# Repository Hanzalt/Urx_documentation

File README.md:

# Urx_documentation
Welcome to the Urx_documentation! You may be wondering what URX is. URX is first completely open source console. This means that if you want to, you can create it by yourself and completly for FREE. The case is printed on a 3D printer. Electrical components are imported from China and from GM electronics.

To find out more, go to the wiki!

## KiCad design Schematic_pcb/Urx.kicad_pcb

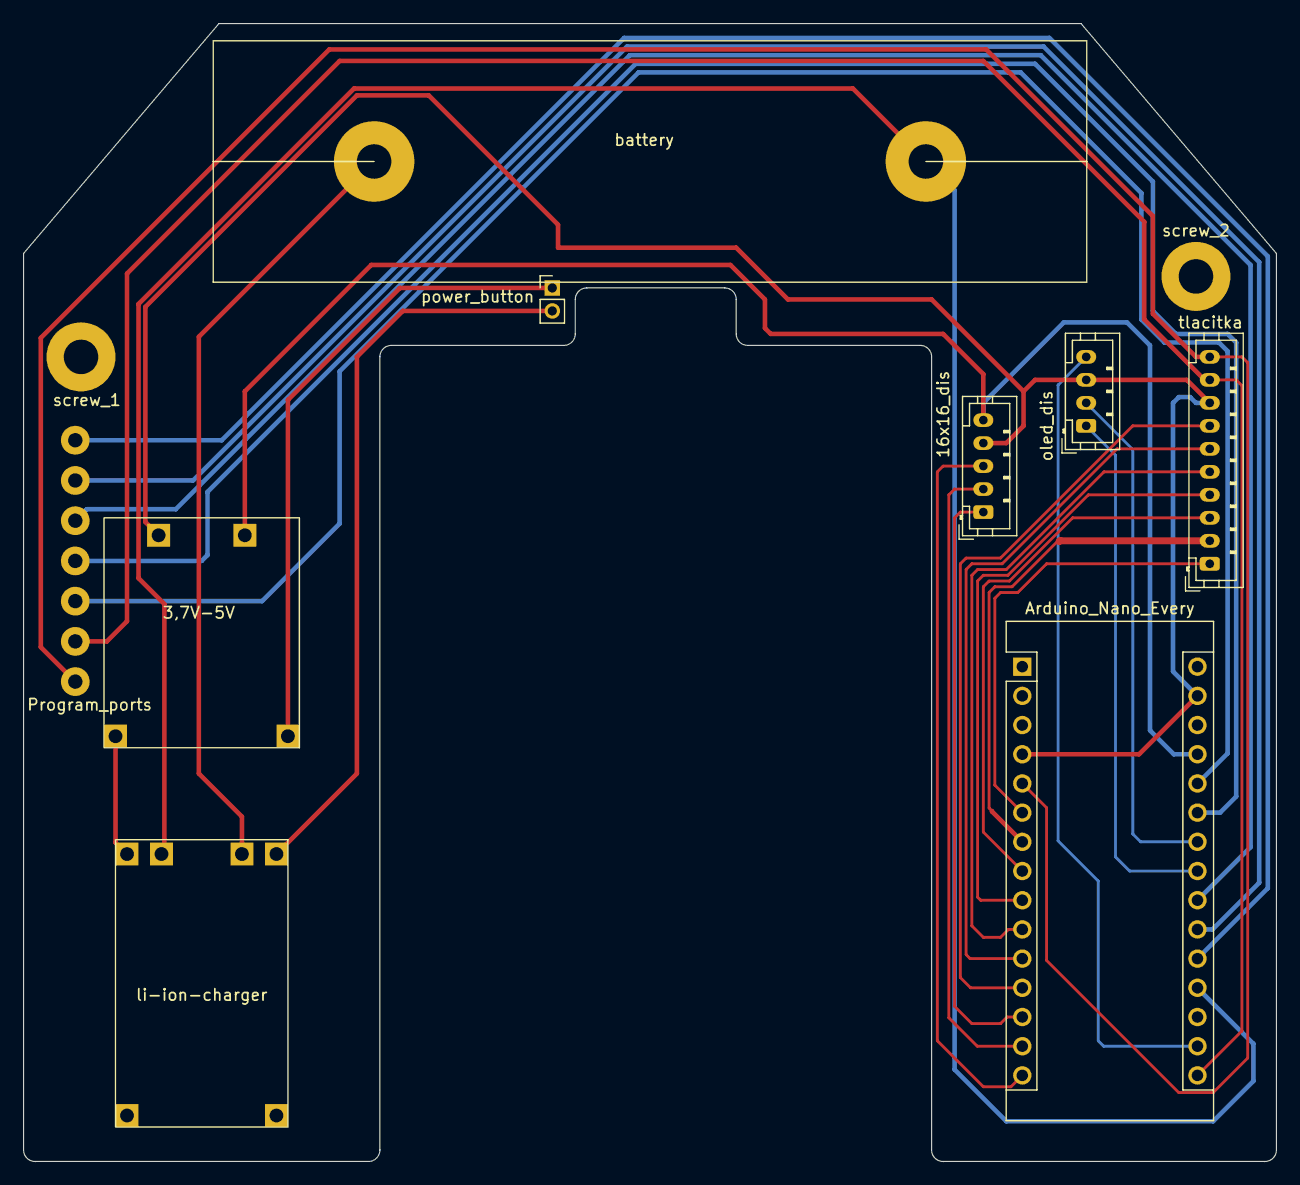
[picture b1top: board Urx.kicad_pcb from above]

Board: 2 copper layers, 109.0 x 99.0 mm, 11 parts (0 on the bottom side), 27 nets.

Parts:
3,7V-5V: boost-to-5v
16x16_dis: 5_pin; JST_PH_B5B-PH-K_1x05_P2.00mm_Vertical
Arduino_Nano_Every: Arduino_Nano_Every; Arduino_Nano
Program_ports: 7_pin
battery: battery_li-ion; li-ion_battery
li-ion-charger: li-ion-charger
oled_dis: 4_pin; JST_PH_B4B-PH-K_1x04_P2.00mm_Vertical
power_button: 2_pin; PinHeader_1x02_P2.00mm_Vertical
screw_1, screw_2: MountingHole_3mm_Pad
tlacitka: 10_pin; JST_PH_B10B-PH-K_1x10_P2.00mm_Vertical

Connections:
2: Arduino_Nano_Every.5 (D2), Program_ports.7 (2), tlacitka.10 (n2)
13: Arduino_Nano_Every.16 (SCK), Program_ports.6 (13), tlacitka.9 (n1)
+3V3: Arduino_Nano_Every.17 (3V3), oled_dis.4 (3,3V)
+5V: 3,7V-5V.1 (5V), 16x16_dis.5 (5V), Arduino_Nano_Every.27 (+5V)
ABat: Arduino_Nano_Every.19 (A0), battery.2 (5V), li-ion-charger.1 (B+)
GND: 3,7V-5V.2 (GND), 16x16_dis.4 (gnd), Arduino_Nano_Every.4 (GND), Arduino_Nano_Every.29 (GND), oled_dis.3 (gnd), tlacitka.8 (gnd)
unnamed: 3,7V-5V.3 (IN+), li-ion-charger.5 (OUT+)
unnamed: 3,7V-5V.4 (IN-), power_button.1 (gnd1)
unnamed: 16x16_dis.1 (cs), Arduino_Nano_Every.13 (D10)
unnamed: 16x16_dis.2 (din), Arduino_Nano_Every.14 (MOSI)
unnamed: 16x16_dis.3 (clk), Arduino_Nano_Every.15 (MISO)
unnamed: Arduino_Nano_Every.6 (D3), tlacitka.1 (b)
unnamed: Arduino_Nano_Every.7 (D4), tlacitka.2 (sound)
unnamed: Arduino_Nano_Every.8 (D5), tlacitka.3 (down)
unnamed: Arduino_Nano_Every.9 (D6), tlacitka.4 (left)
unnamed: Arduino_Nano_Every.10 (D7), tlacitka.5 (forward)
unnamed: Arduino_Nano_Every.11 (D8), tlacitka.6 (right)
unnamed: Arduino_Nano_Every.12 (D9), tlacitka.7 (a)
unnamed: Arduino_Nano_Every.20 (A1), Program_ports.1 (A1)
unnamed: Arduino_Nano_Every.21 (A2), Program_ports.2 (A2)
unnamed: Arduino_Nano_Every.22 (A3), Program_ports.3 (A3)
unnamed: Arduino_Nano_Every.23 (SDA/A4), oled_dis.1 (sda)
unnamed: Arduino_Nano_Every.24 (SCL/A5), oled_dis.2 (csk)
unnamed: Arduino_Nano_Every.25 (A6), Program_ports.4 (A6)
unnamed: Arduino_Nano_Every.26 (A7), Program_ports.5 (A7)
unnamed: battery.1 (gnd), li-ion-charger.2 (B-)
unnamed: li-ion-charger.6 (OUT-), power_button.2 (gnd2)

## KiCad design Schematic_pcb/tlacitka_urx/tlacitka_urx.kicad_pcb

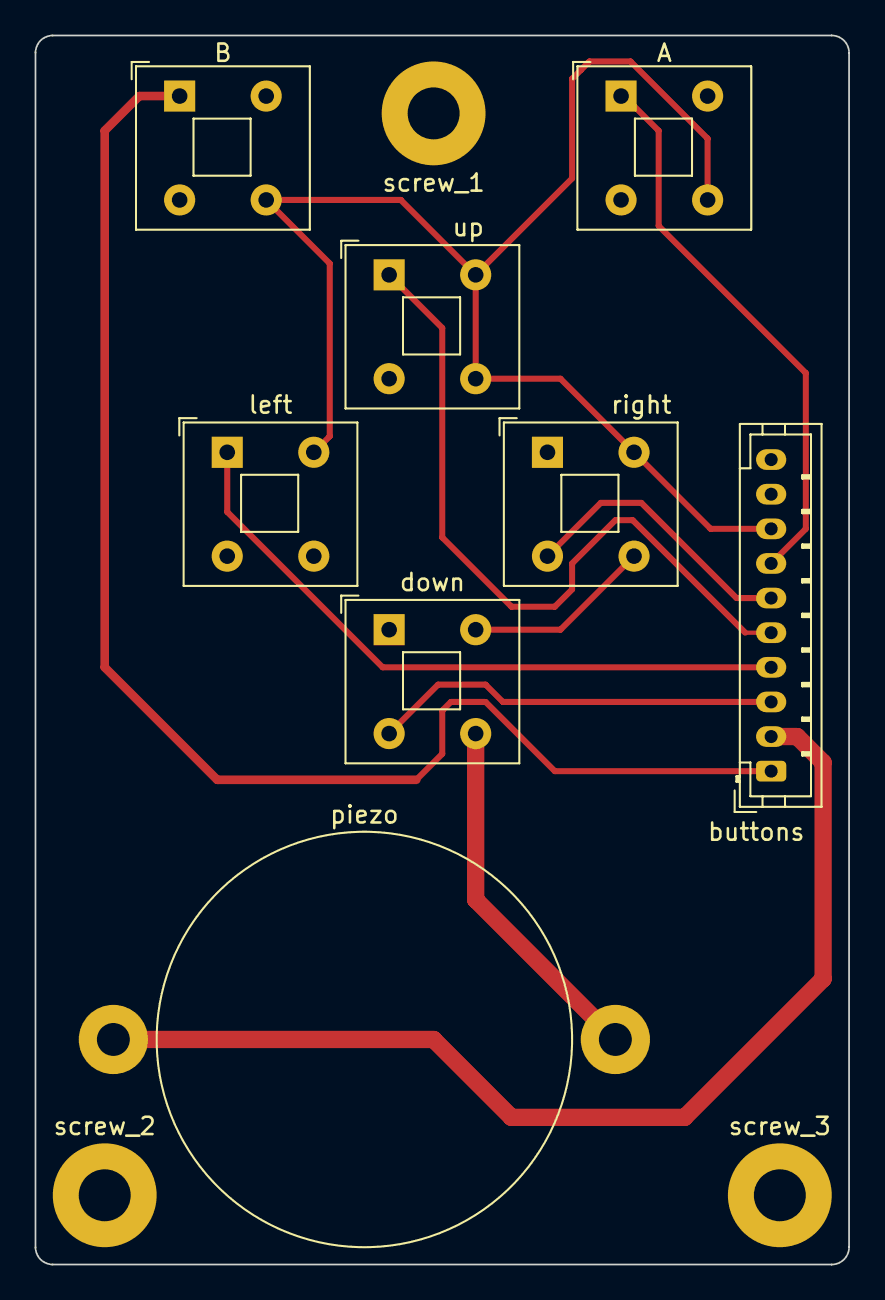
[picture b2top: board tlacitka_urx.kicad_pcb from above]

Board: 2 copper layers, 47.0 x 71.0 mm, 11 parts (0 on the bottom side), 10 nets.

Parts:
A: SW_Push_Dual; SW_Push_2P1T_Toggle_CK_PVA1xxH1xxxxxxV2
B: SW_Push_Dual; SW_Push_2P1T_Toggle_CK_PVA1xxH1xxxxxxV2
buttons: 10_pin; JST_PH_B10B-PH-K_1x10_P2.00mm_Vertical
down: SW_Push_Dual; SW_Push_2P1T_Toggle_CK_PVA1xxH1xxxxxxV2
left: SW_Push_Dual; SW_Push_2P1T_Toggle_CK_PVA1xxH1xxxxxxV2
piezo: Piezo_KPEG110
right: SW_Push_Dual; SW_Push_2P1T_Toggle_CK_PVA1xxH1xxxxxxV2
screw_1, screw_2, screw_3: MountingHole_3mm_Pad
up: SW_Push_Dual; SW_Push_2P1T_Toggle_CK_PVA1xxH1xxxxxxV2

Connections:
unnamed: A.1, buttons.7 (a)
unnamed: A.4, B.4, buttons.8 (gnd), left.2, right.2, up.2, up.4
unnamed: B.1, buttons.1 (b)
unnamed: down.2, right.4
unnamed: buttons.3 (down), down.3
unnamed: buttons.4 (left), left.1
unnamed: down.4, piezo.1 (Gnd)
unnamed: buttons.6 (right), right.3
unnamed: buttons.2 (sound), piezo.2
unnamed: buttons.5 (forward), up.1

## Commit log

2022-02-22 Create PCB_naming
2022-02-22 Update PCB_naming
    adding din
2022-05-04 0-4
    urxos_0-4
    +Galaxian
    +nove menu
    -Dekuje e
2022-08-10 Vytvoreni knihovny
    +Snaha o vytvoreni jedne knihovny - co nejjednoduseji udelany kod - vse schovany v jedne knihovne (inicializace, funkce)
    +Vytvoreni testovaciho kodu
    +Zip soubor knihoven
2022-08-12 nefunkcni pokus s knihovnou
2022-08-21 test
2022-08-21 Funkcni verze s knihovnou v1
2022-08-25 Snaha o udelani interruptu
    Nakonec jsem zjistil ze to je hardwerova chyba
2022-08-25 Smazal jsem space invators
2022-08-26 BIG UPDATE
    Zmeneny nazev z code na urxos. Zmeneny vykreslovaci algoritmus.
    Zmeneny ikonky,
    Zmeneny opening animation - logo a znelka
2022-08-27 Verze 0.6.0
    Zmeneny vsechny vykreslovaci funkce.
    Opraveno vsechno vykreslovani.
    Predelani zvuku.
    Dalsi opravy chyb
2022-08-28 Nastaveni a male zmeny
2022-08-28 Urx_0_6_1_library
2022-08-30 Settings
2022-08-30 DanceMan basic functionality
2022-08-31 DanceMan
    Vytvoreni dance mana
2022-08-31 UrxLibrary 0.7.9
2022-09-02 MIni update
2022-09-10 Making folders
2022-09-18 Flip display and library update
    I needed to flip display because I change the position of display (OLED 0.91"). Finally I managed to make one library.
2022-09-18 Rename folder code to Firmware
    I renamed folder code to Firmware because it was similar as github button code
2022-09-18 URXos_library_0-7-92
2022-10-08 Sound
    Turning sound off in Dance man when it should be turned off.
2022-10-11 Models
2022-10-11 Models_update
2022-10-21 score display mistake
2022-10-26 Library_0.7.9.3
    BIG library change - size of library decreased from 10.5 MB to 71.8 KB.
2022-10-27 Mistake-slower/bigger
2022-10-27 Revert "Mistake-slower/bigger"
    This reverts commit 092e83d06186fa26a2ec9a688647ae0a62e0e741.
2022-10-28 1. Removed file PCB_naming it was not important. 2. Remaped battery indicator. 3. new Difficulty tab in settings.
2022-10-28 1. Difficulty 2. Finally I managed to repair Danceman. YES
2022-10-29 1. app names 2. new gamemode selection in snake 3. new gamemode in snake - snake SUPER - snake with another food type
2022-10-29 1. New library 2. New readme in libraries
2022-10-29 1. Changed Medium intensity 2. Repaired bug in galaxian - sound
2022-11-01 1. bug fixes 2. DanceMan modes
2022-11-03 1. New songs 2. Big Galaxian update 3. New danceman songs
2022-11-04 1. Galaxian modes 2. New songs - Doom, Bloody tears 3. Bug fixes - high score menu
2022-11-07 1. New highscore celebration 2. sound bug fixes
2022-11-28 Comments 1
    I added comments for variables and functions
2022-12-02 Version 0.8.1
    Sleep function
2023-06-09 Schematics and pcb design
2023-06-09 KiCad_library
2023-06-11 Renaming and Hardware list
2025-01-04 Version 0.8.3
    new button_pcb therefore the interrupt behaviour needs to be flipped
2025-01-15 New models
